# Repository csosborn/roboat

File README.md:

# Roboat!

An autonomous, solar-powered boat. An RP2040 microcontroller handles power monitoring and control and supervises a Raspberry Pi, which provides data storage, navigation, planning, and communications.

## Design documents

- [Compute.md](Compute.md): compute architecture and the power-management state machine
- [PowerSystem.md](PowerSystem.md): battery, charge controller, and solar array selection
- [SolarArrayTrade.md](SolarArrayTrade.md): solar array trade study

## Repository layout

| Path | Contents |
| --- | --- |
| `src/micro/` | MicroPython code for the RP2040 Feather (power FSM, Victron MPPT, INA260, Pi link) |
| `src/pi/` | Raspberry Pi monitor service, TIG stack (Telegraf/InfluxDB/Grafana), and systemd units; see [setup notes](src/pi/TIG/setup.md) |
| `src/build-tools/` | Docker container for building custom MicroPython firmware |
| `printed_parts/` | STL files for 3D-printed parts |
| `take1/` | The original Arduino/Eagle-based attempt, kept for reference |

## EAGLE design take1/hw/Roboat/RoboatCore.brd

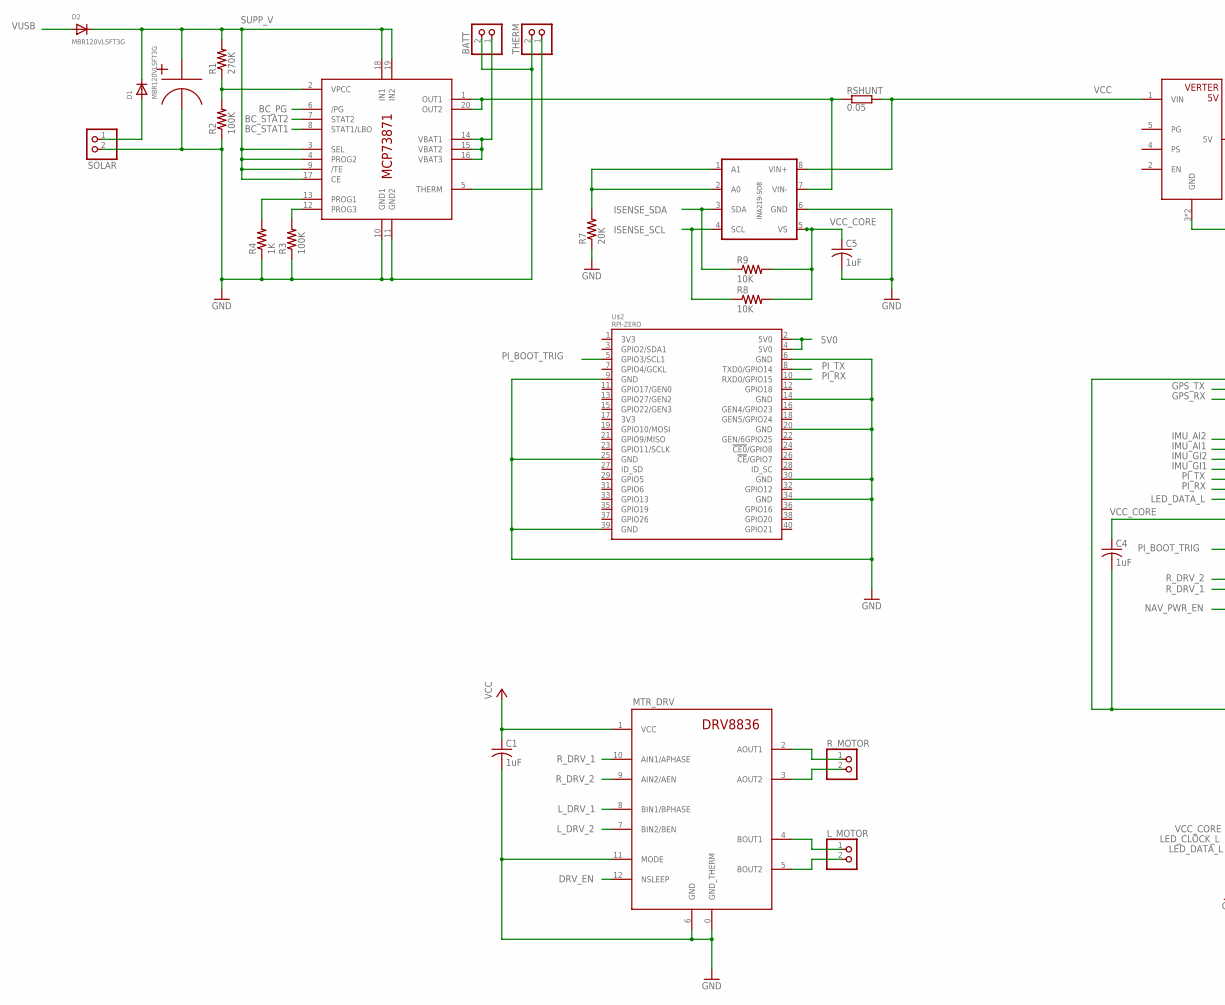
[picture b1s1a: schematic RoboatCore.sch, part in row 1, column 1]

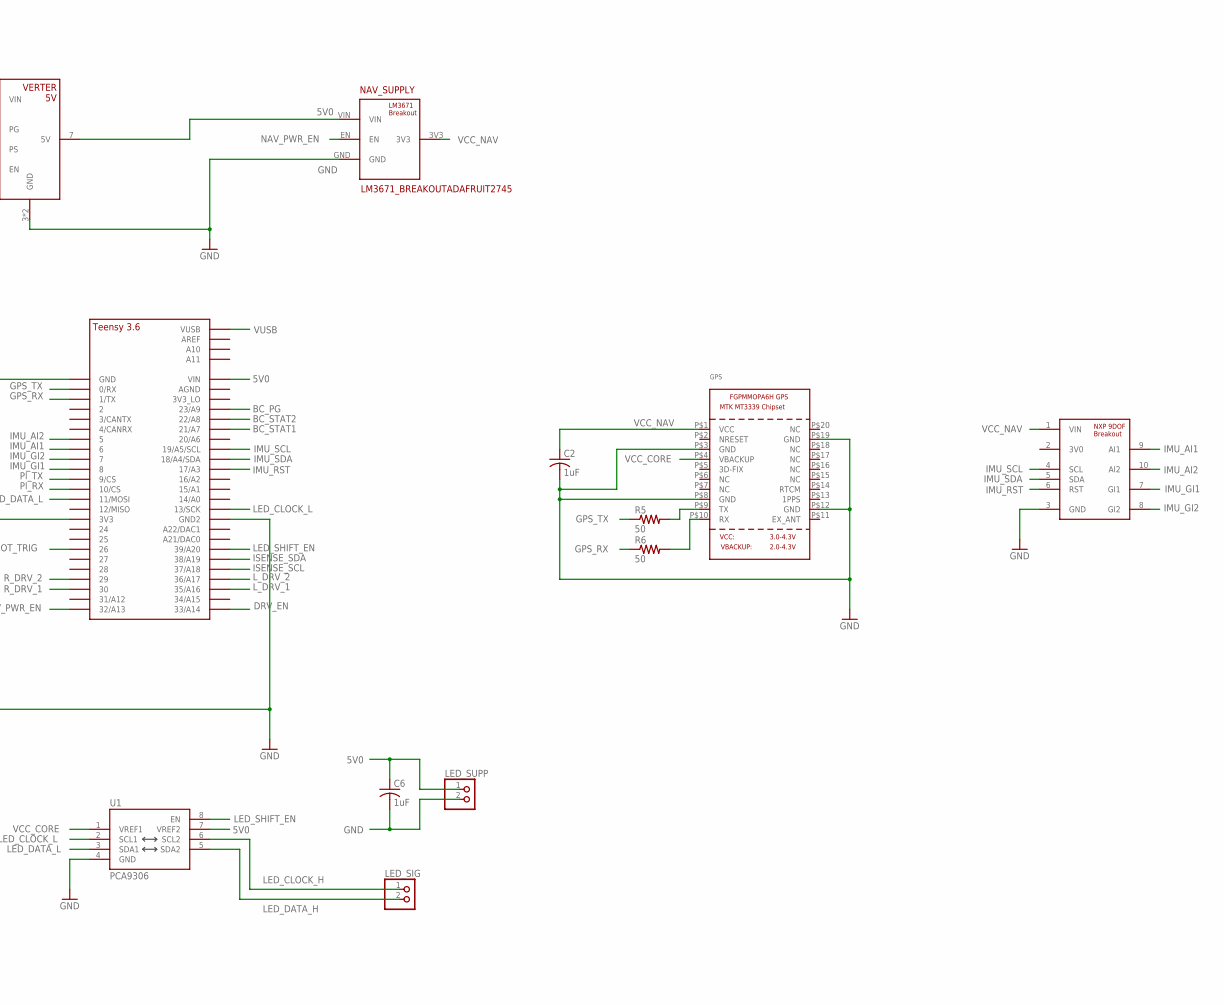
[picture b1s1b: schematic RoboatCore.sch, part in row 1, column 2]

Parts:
BATT: JST_2PIN-SMT-RA; JST-PH-2-SMT-RA
C1, C2, C4, C5, C6: 1uF; C0603
C3: 2200uF; 2200UF_CAN
D1, D2: MBR120VLSFT3G; SOD-123
GPS: GPS_FGPMMOPA6H; FGPMMOPA6H
IC2: MCP73871; QFN20
INA219: INA219-SO8D; SO08
LED_SIG: PINHD-1X2; 1X02
LED_SUPP: PINHD-1X2; 1X02
L_MOTOR: PINHD-1X2; 1X02
MTR_DRV: DRV8836DRV8836DSSR; WSON-12
NAV_SUPPLY: LM3671_BREAKOUTADAFRUIT2745; LM3671_BREAKOUT
R1: 270K; R0603
R2, R3: 100K; R0603
R4: 1K; R0603
R5, R6: 50; R0603
R7: 20K; R0603
R8, R9: 10K; R0603
RSHUNT: 0.05; SMK
R_MOTOR: PINHD-1X2; 1X02
SOLAR: JST_2PIN-SMT-RA; JST-PH-2-SMT-RA
THERM: JST_2PIN-SMT-RA; JST-PH-2-SMT-RA
U1: PCA9306; PSOP-8
U$1: TEENSY_3.5/3.6_BASIC
U$2: RPI-ZERO; RASP_PI_ZERO_BOARD_FULL
U$3: NXP_9DOF_BREAKOUTADAFRUIT3463; NXP_9DOF_BREAKOUT
U$4: VERTER_5VADAFRUIT2190; VERTER_5V

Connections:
5V0: C6.1, LED_SUPP.1, NAV_SUPPLY.VIN, U1.7 (VREF2), U$1.VIN, U$2.2 (5V0), U$2.4 (5V0), U$4.7 (5V)
BATT_NTC: IC2.5 (THERM), THERM.1 (2)
BC_PG: IC2.6 (/PG), U$1.23/A9
BC_STAT1: IC2.8 (STAT1/LBO), U$1.21/A7
BC_STAT2: IC2.7 (STAT2), U$1.22/A8
DRV_EN: MTR_DRV.12 (NSLEEP), U$1.33/A14
GND: BATT.2 (1), C1.2, C2.2, C3.2 (NEG), C4.2, C5.2, C6.2, GPS.P$3 (GND), GPS.P$8 (GND), GPS.P$12 (GND), GPS.P$19 (GND), IC2.10 (GND1), IC2.11 (GND2), INA219.6 (GND), LED_SUPP.2, MTR_DRV.0 (GND_THERM), MTR_DRV.6 (GND), MTR_DRV.11 (MODE), NAV_SUPPLY.GND, R2.1, R3.1, R4.1, R7.1, SOLAR.2 (1), THERM.2 (1), U1.4 (GND), U$1.GND, U$1.GND2, U$2.6 (GND), U$2.9 (GND), U$2.14 (GND), U$2.20 (GND), U$2.25 (GND), U$2.30 (GND), U$2.34 (GND), U$2.39 (GND), U$3.3 (GND), U$4.3 (GND), U$4.6 (GND)
GPS_RX: R6.1, U$1.1/TX
GPS_RX_I: GPS.P$10 (RX), R6.2
GPS_TX: R5.1, U$1.0/RX
GPS_TX_O: GPS.P$9 (TX), R5.2
IMU_AI1: U$1.6, U$3.9 (AI1)
IMU_AI2: U$1.5, U$3.10 (AI2)
IMU_GI1: U$1.8, U$3.7 (GI1)
IMU_GI2: U$1.7, U$3.8 (GI2)
IMU_RST: U$1.17/A3, U$3.6 (RST)
IMU_SCL: U$1.19/A5/SCL, U$3.4 (SCL)
IMU_SDA: U$1.18/A4/SDA, U$3.5 (SDA)
ISENSE_SCL: INA219.4 (SCL), R8.1, U$1.37/A18
ISENSE_SDA: INA219.3 (SDA), R9.1, U$1.38/A19
LED_CLOCK_H: LED_SIG.1, U1.6 (SCL2)
LED_CLOCK_L: U1.2 (SCL1), U$1.13/SCK
LED_DATA_H: LED_SIG.2, U1.5 (SDA2)
LED_DATA_L: U1.3 (SDA1), U$1.11/MOSI
LED_SHIFT_EN: U1.8 (EN), U$1.39/A20
L_DRV_1: MTR_DRV.8 (BIN1/BPHASE), U$1.35/A16
L_DRV_2: MTR_DRV.7 (BIN2/BEN), U$1.36/A17
unnamed: MTR_DRV.2 (AOUT1), R_MOTOR.1
unnamed: MTR_DRV.3 (AOUT2), R_MOTOR.2
unnamed: IC2.2 (VPCC), R1.1, R2.2
unnamed: L_MOTOR.1, MTR_DRV.4 (BOUT1)
unnamed: L_MOTOR.2, MTR_DRV.5 (BOUT2)
unnamed: INA219.1 (A1), INA219.2 (A0), R7.2
unnamed: BATT.1 (2), IC2.14 (VBAT1), IC2.15 (VBAT2), IC2.16 (VBAT3)
unnamed: IC2.12 (PROG3), R3.2
unnamed: IC2.13 (PROG1), R4.2
NAV_PWR_EN: NAV_SUPPLY.EN, U$1.32/A13
PI_BOOT_TRIG: U$1.26, U$2.5 (GPIO3/SCL1)
PI_RX: U$1.10/CS, U$2.10 (RXD0/GPIO15)
PI_TX: U$1.9/CS, U$2.8 (TXD0/GPIO14)
R_DRV_1: MTR_DRV.10 (AIN1/APHASE), U$1.30
R_DRV_2: MTR_DRV.9 (AIN2/AEN), U$1.29
SOLAR_V_RAW: D1.A, SOLAR.1 (2)
SUPP_V: C3.1 (POS), D1.C, D2.C, IC2.3 (SEL), IC2.4 (PROG2), IC2.9 (/TE), IC2.17 (CE), IC2.18 (IN1), IC2.19 (IN2), R1.2
VBUS: IC2.1 (OUT1), IC2.20 (OUT2), INA219.7 (VIN-), RSHUNT.2
VCC: C1.1, INA219.8 (VIN+), MTR_DRV.1 (VCC), RSHUNT.1, U$4.1 (VIN)
VCC_CORE: C4.1, C5.1, GPS.P$4 (VBACKUP), INA219.5 (VS), R8.2, R9.2, U1.1 (VREF1), U$1.3V3
VCC_NAV: C2.1, GPS.P$1 (VCC), NAV_SUPPLY.3V3, U$3.1 (VIN)
VUSB: D2.A, U$1.VUSB

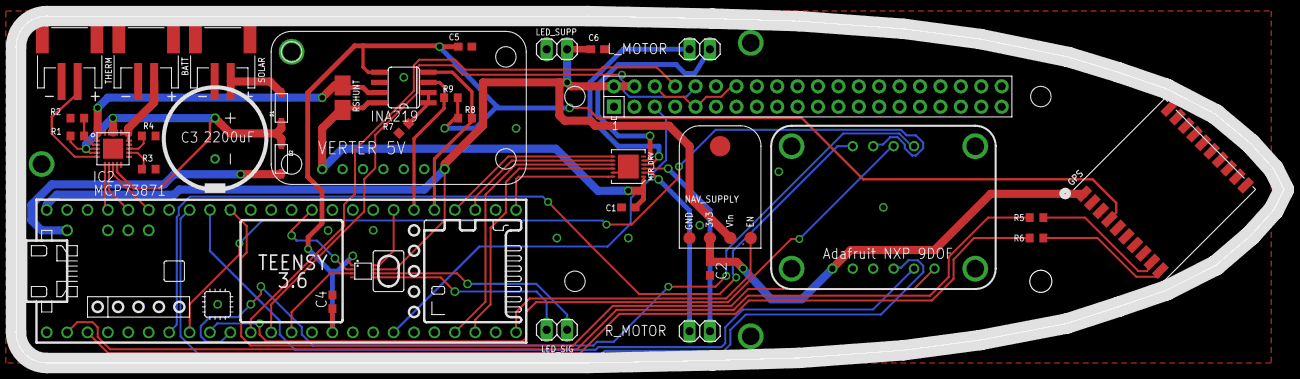
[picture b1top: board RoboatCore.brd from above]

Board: 2 copper layers, 157.8 x 43.2 mm, 35 parts (0 on the bottom side), 49 nets.

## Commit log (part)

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2017-09-11 First commit, with notes and initial Arduino code skeleton.
2017-10-14 Tinkering with the Pilot module firmware.
2017-11-06 Added PCB and related Eagle libraries.
2017-11-06 Updated Arduino code with new pin assignments from PCB.
2017-11-13 All parts accounted for.
2017-12-23 Added initial AHRS state machine to Pilot module.
2017-12-24 Factored Roboat::StateMachine out of Roboat::AHRS.
2017-12-24 Added PowerManager state machine to Pilot module.
2017-12-26 Rearranged initializer lists to avoid reorder warnings
2018-01-02 Refactoring, cleanup, const-correctness
2018-01-08 Factored GPS code into RoboatGPSManager state machine
2018-01-08 Sketched out Captain state machine. More refactoring.
2018-01-27 Small corrections.
2019-03-03 Initial captain skeleton and connection to helm.
2019-03-04 Cleaned up CMake/Conan approach, added SQLite.
2019-03-04 Early experiments with SQLite-based persistence.
2019-03-05 Added prepared statement step() method.
2024-10-24 Move abandoned prehistory to take1 directory.
2024-10-24 Some basic notes on Roboat, take 2.
2024-10-24 Basic containerized TIG stack.
2024-10-24 Don't ignore src/pi.
2024-10-24 Initial scratch work on RP2040.
2024-10-24 Initial scratch work on Pi side.
2024-10-24 Omit Grafana pending memory upgrade.
2024-12-02 TIG stack and supporting systemd units.
2024-12-02 RP2040 micropython lib directory.
2024-12-02 RPi-based monitor program (not yet containerized)
2024-12-02 Some updated notes on the power control state machine.
2024-12-02 Grafana dashboard definition.
2024-12-02 A bunch of disorganized changes to the RP2040 code.
2024-12-14 Added micropython-builder container.
2024-12-14 Remove incorrectly added submodules.
2025-06-19 A initial quite mediocre SoC estimator.
2025-06-19 Avionics testbed and sync util.

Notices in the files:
parts and their libraries:
SparkFun-IC-Comms: Licensing: Creative Commons ShareAlike 4.0 International - https://creativecommons.org/licenses/by-sa/4.0
